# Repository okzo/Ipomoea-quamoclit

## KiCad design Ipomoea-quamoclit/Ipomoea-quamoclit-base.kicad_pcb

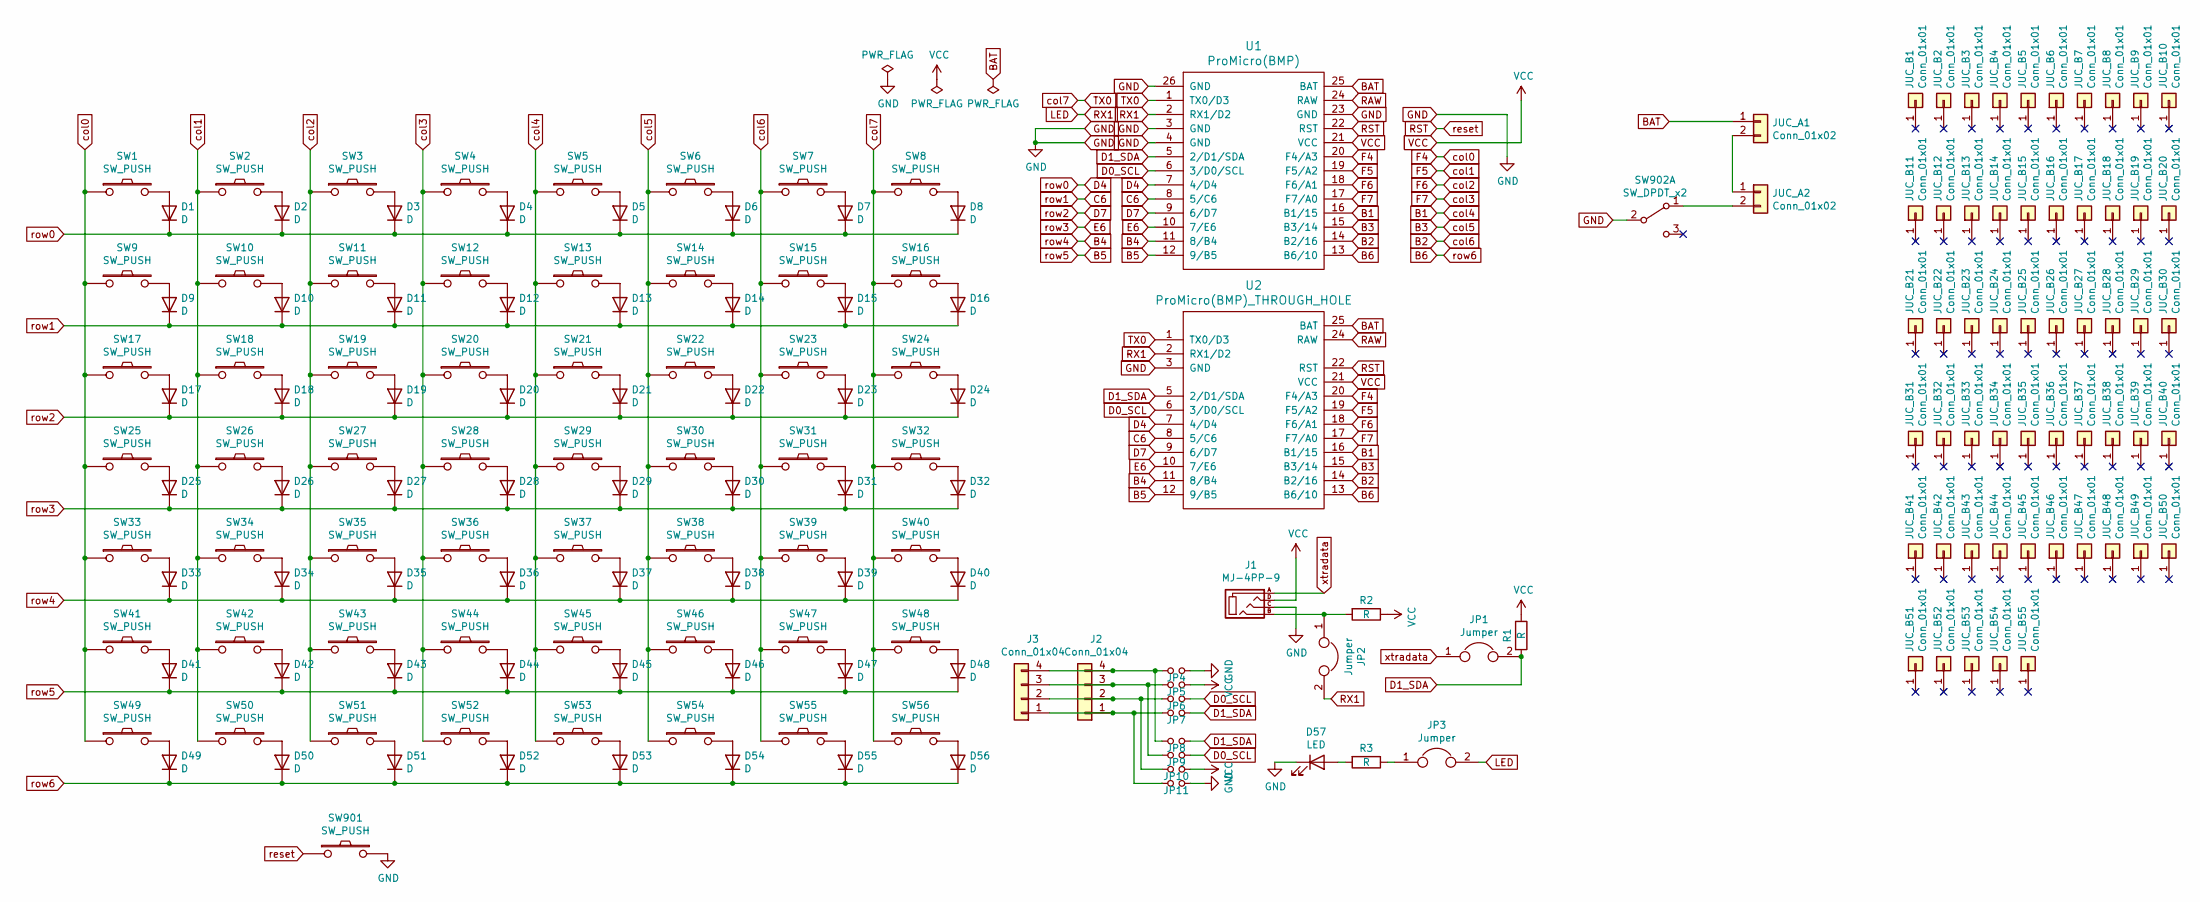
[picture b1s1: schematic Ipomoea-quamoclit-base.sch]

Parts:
D1, D2, D3, D4, D5, D6, D7, D8, D9, D10, D11, D12, D13, D14, D15, D16, D17, D18, D19, D20, D21, D22, D23, D24, D25, D26, D27, D28, D29, D30, D31, D32, D33, D34, D35, D36, D37, D38, D39, D40, D41, D42, D43, D44, D45, D46, D47, D48, D49, D50, D51, D52, D53, D54, D55, D56: D; D3_SMD
D57: LED; LED_D3.0mm
J1: MJ-4PP-9
J2, J3: Conn_01x04; OLED
JP1, JP2, JP3: Jumper
JP4, JP5, JP6, JP7, JP8, JP9, JP10, JP11: Jumper_1side
JUC_A1, JUC_A2: Conn_01x02; BH-411-4P24
JUC_B1, JUC_B2, JUC_B3, JUC_B4, JUC_B5, JUC_B6, JUC_B7, JUC_B8, JUC_B9, JUC_B10, JUC_B11, JUC_B12, JUC_B13, JUC_B14, JUC_B15, JUC_B16, JUC_B17, JUC_B18, JUC_B19, JUC_B20, JUC_B21, JUC_B22, JUC_B23, JUC_B24, JUC_B25, JUC_B26, JUC_B27, JUC_B28, JUC_B29, JUC_B30, JUC_B31, JUC_B32, JUC_B33, JUC_B34, JUC_B35, JUC_B36, JUC_B37, JUC_B38, JUC_B39, JUC_B40, JUC_B41, JUC_B42, JUC_B43, JUC_B44, JUC_B45, JUC_B46, JUC_B47, JUC_B48, JUC_B49, JUC_B50, JUC_B51, JUC_B52, JUC_B53, JUC_B54, JUC_B55: Conn_01x01; Ipomoea-quamoclit_Base_TH_2_Cx1
R1, R2, R3: R
SW1, SW2, SW3, SW4, SW5, SW6, SW7, SW8, SW9, SW10, SW11, SW12, SW13, SW14, SW15, SW16, SW17, SW18, SW19, SW20, SW21, SW22, SW23, SW24, SW25, SW26, SW27, SW28, SW29, SW30, SW31, SW32, SW33, SW34, SW35, SW36, SW37, SW38, SW39, SW40, SW41, SW42, SW43, SW44, SW45, SW46, SW47, SW48, SW49, SW50, SW51, SW52, SW53, SW54, SW55, SW56: SW_PUSH; Ipomoea-quamoclit_Base_CherryMX_NoDioade
SW901: SW_PUSH; ResetSW
SW902: SW_DPDT_x2; SlideSwitch
U1: ProMicro(BMP)
U2: ProMicro(BMP)_THROUGH_HOLE

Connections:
B1: SW5.1, SW13.1, SW21.1, SW29.1, SW37.1, SW45.1, SW53.1, U1.16 (B1/15), U2.16 (B1/15)
B2: SW7.1, SW15.1, SW23.1, SW31.1, SW39.1, SW47.1, SW55.1, U1.14 (B2/16), U2.14 (B2/16)
B3: SW6.1, SW14.1, SW22.1, SW30.1, SW38.1, SW46.1, SW54.1, U1.15 (B3/14), U2.15 (B3/14)
B4: D33.1 (K), D34.1 (K), D35.1 (K), D36.1 (K), D37.1 (K), D38.1 (K), D39.1 (K), D40.1 (K), U1.11 (8/B4), U2.11 (8/B4)
B5: D41.1 (K), D42.1 (K), D43.1 (K), D44.1 (K), D45.1 (K), D46.1 (K), D47.1 (K), D48.1 (K), U1.12 (9/B5), U2.12 (9/B5)
B6: D49.1 (K), D50.1 (K), D51.1 (K), D52.1 (K), D53.1 (K), D54.1 (K), D55.1 (K), D56.1 (K), U1.13 (B6/10), U2.13 (B6/10)
BAT: JUC_A1.1, U1.25 (BAT), U2.25 (BAT)
C6: D9.1 (K), D10.1 (K), D11.1 (K), D12.1 (K), D13.1 (K), D14.1 (K), D15.1 (K), D16.1 (K), U1.8 (5/C6), U2.8 (5/C6)
D0_SCL: JP6.1, JP9.1, U1.6 (3/D0/SCL), U2.6 (3/D0/SCL)
D1_SDA: JP1.2, JP7.1, JP8.1, R1.2, U1.5 (2/D1/SDA), U2.5 (2/D1/SDA)
D4: D1.1 (K), D2.1 (K), D3.1 (K), D4.1 (K), D5.1 (K), D6.1 (K), D7.1 (K), D8.1 (K), U1.7 (4/D4), U2.7 (4/D4)
D7: D17.1 (K), D18.1 (K), D19.1 (K), D20.1 (K), D21.1 (K), D22.1 (K), D23.1 (K), D24.1 (K), U1.9 (6/D7), U2.9 (6/D7)
E6: D25.1 (K), D26.1 (K), D27.1 (K), D28.1 (K), D29.1 (K), D30.1 (K), D31.1 (K), D32.1 (K), U1.10 (7/E6), U2.10 (7/E6)
F4: SW1.1, SW9.1, SW17.1, SW25.1, SW33.1, SW41.1, SW49.1, U1.20 (F4/A3), U2.20 (F4/A3)
F5: SW2.1, SW10.1, SW18.1, SW26.1, SW34.1, SW42.1, SW50.1, U1.19 (F5/A2), U2.19 (F5/A2)
F6: SW3.1, SW11.1, SW19.1, SW27.1, SW35.1, SW43.1, SW51.1, U1.18 (F6/A1), U2.18 (F6/A1)
F7: SW4.1, SW12.1, SW20.1, SW28.1, SW36.1, SW44.1, SW52.1, U1.17 (F7/A0), U2.17 (F7/A0)
GND: D57.1 (K), J1.C, JP4.1, JP11.1, SW901.2, SW902.2 (B), U1.3 (GND), U1.4 (GND), U1.23 (GND), U1.26 (GND), U2.3 (GND)
LED: JP2.2, JP3.2, U1.2 (RX1/D2), U2.2 (RX1/D2)
unnamed: D1.2 (A), SW1.2
unnamed: D2.2 (A), SW2.2
unnamed: D3.2 (A), SW3.2
unnamed: D4.2 (A), SW4.2
unnamed: D5.2 (A), SW5.2
unnamed: D6.2 (A), SW6.2
unnamed: D7.2 (A), SW7.2
unnamed: D8.2 (A), SW8.2
unnamed: D9.2 (A), SW9.2
unnamed: D10.2 (A), SW10.2
unnamed: D11.2 (A), SW11.2
unnamed: D12.2 (A), SW12.2
unnamed: D13.2 (A), SW13.2
unnamed: D14.2 (A), SW14.2
unnamed: D15.2 (A), SW15.2
unnamed: D16.2 (A), SW16.2
unnamed: D17.2 (A), SW17.2
unnamed: D18.2 (A), SW18.2
unnamed: D19.2 (A), SW19.2
unnamed: D20.2 (A), SW20.2
unnamed: D21.2 (A), SW21.2
unnamed: D22.2 (A), SW22.2
unnamed: D23.2 (A), SW23.2
unnamed: D24.2 (A), SW24.2
unnamed: D25.2 (A), SW25.2
unnamed: D26.2 (A), SW26.2
unnamed: D27.2 (A), SW27.2
unnamed: D28.2 (A), SW28.2
unnamed: D29.2 (A), SW29.2
unnamed: D30.2 (A), SW30.2
unnamed: D31.2 (A), SW31.2
unnamed: D32.2 (A), SW32.2
unnamed: D33.2 (A), SW33.2
unnamed: D34.2 (A), SW34.2
unnamed: D35.2 (A), SW35.2
unnamed: D36.2 (A), SW36.2
unnamed: D37.2 (A), SW37.2
unnamed: D38.2 (A), SW38.2
unnamed: D39.2 (A), SW39.2
unnamed: D40.2 (A), SW40.2
unnamed: D41.2 (A), SW41.2
unnamed: D42.2 (A), SW42.2
unnamed: D43.2 (A), SW43.2
unnamed: D44.2 (A), SW44.2
unnamed: D45.2 (A), SW45.2
unnamed: D46.2 (A), SW46.2
unnamed: D47.2 (A), SW47.2
unnamed: D48.2 (A), SW48.2
unnamed: D49.2 (A), SW49.2
unnamed: D50.2 (A), SW50.2
unnamed: D51.2 (A), SW51.2
unnamed: D52.2 (A), SW52.2
unnamed: D53.2 (A), SW53.2
unnamed: D54.2 (A), SW54.2
unnamed: D55.2 (A), SW55.2
unnamed: D56.2 (A), SW56.2
unnamed: D57.2 (A), R3.2
unnamed: J1.B, JP2.1, R2.2
unnamed: J2.1, J3.1, JP7.2, JP11.2
unnamed: J2.2, J3.2, JP6.2, JP10.2
unnamed: J2.3, J3.3, JP5.2, JP9.2
unnamed: J2.4, J3.4, JP4.2, JP8.2
unnamed: JP3.1, R3.1
unnamed: JUC_A1.2, JUC_A2.1
unnamed: JUC_A2.2, SW902.1 (A)
RAW: U1.24 (RAW), U2.24 (RAW)
RST: SW901.1, U1.22 (RST), U2.22 (RST)
TX0: SW8.1, SW16.1, SW24.1, SW32.1, SW40.1, SW48.1, SW56.1, U1.1 (TX0/D3), U2.1 (TX0/D3)
VCC: J1.D, JP5.1, JP10.1, R1.1, R2.1, U1.21 (VCC), U2.21 (VCC)
xtradata: J1.A, JP1.1

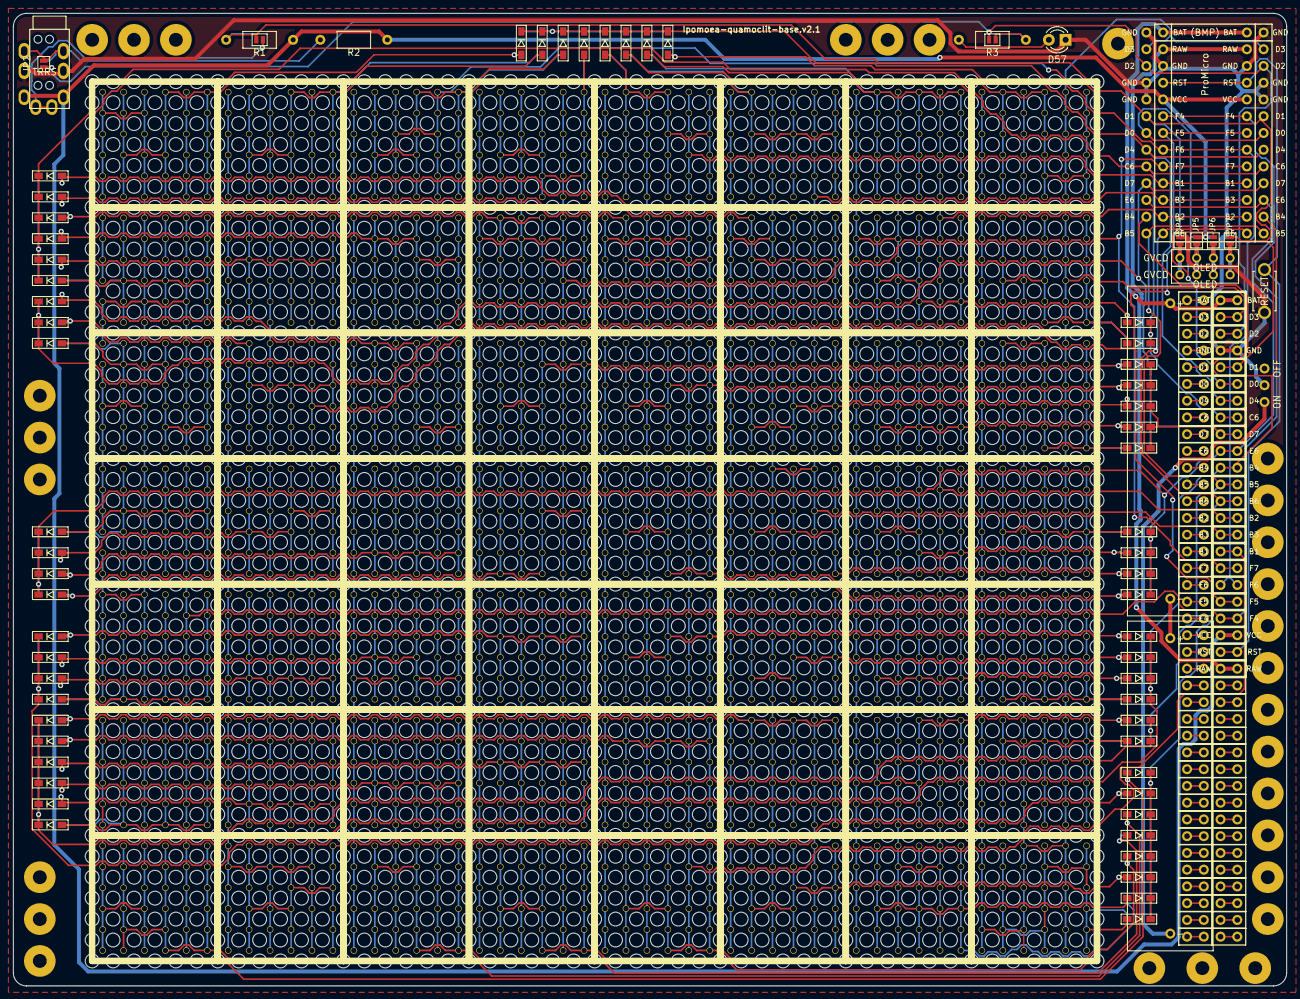
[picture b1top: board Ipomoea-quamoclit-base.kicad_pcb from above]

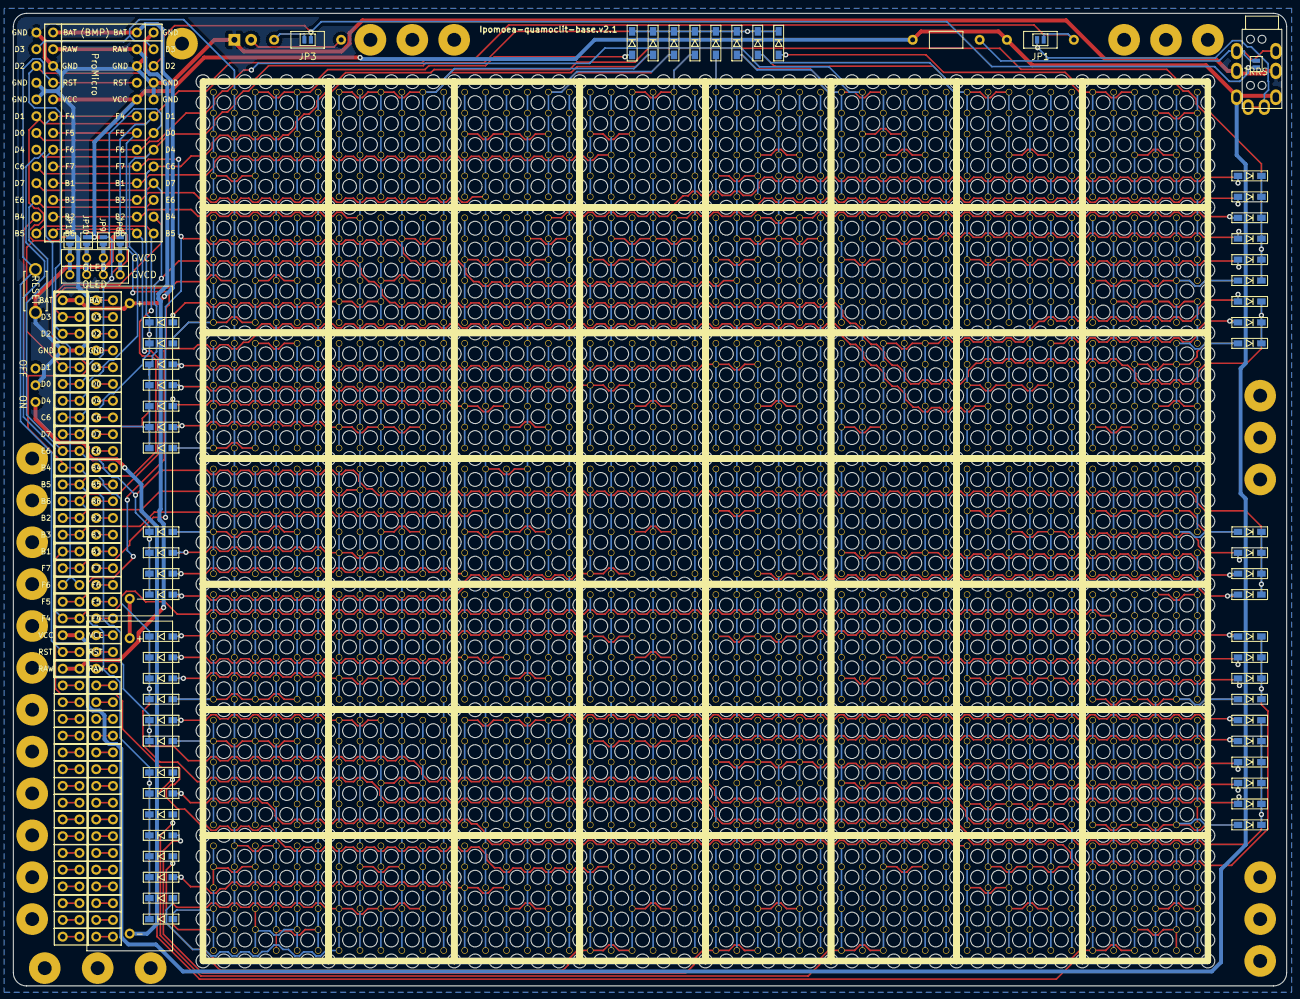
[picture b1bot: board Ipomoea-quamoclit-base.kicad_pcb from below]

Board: 2 copper layers, 193.1 x 147.5 mm, 191 parts (7 on the bottom side), 89 nets.

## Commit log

2021-09-09 add projects
